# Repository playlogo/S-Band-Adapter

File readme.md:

# S-Band Adapter

*(image might be outdated, check interactive viewer for latest version)*

**Notes:**

- Under 10x10 cm
- Designed to get stacked *on top* of the S-Band module
- Passes ERC & DRC

**Links:**

- [Interactive PCB View (powered by KiCanvas, always up to date)](https://kicanvas.org/?repo=https%3A%2F%2Fgithub.com%2Fplaylogo%2FS-Band-Adapter%2Ftree%2Fmaster%2Fpcb%2FS-Band%2520Adapter)

## Components

**SMD Parts:**

- 2x [`CT3151SP`](https://www.digikey.de/de/products/detail/cal-test-electronics/CT3151SP-2/6005547): Banana plugs for VBat & GND - *[footprint](https://componentsearchengine.com/part-view/CT3151SP-2/Cal%20Test)*
- 1x [`FTSH‑107‑01‑L‑DV‑K‑A`](https://www.digikey.de/de/products/detail/samtec-inc/FTSH-107-01-L-DV-K-A/7443623): ST-Link debug connector, uses UART A from PC104 - *[footprint](https://www.snapeda.com/parts/FTSH-107-01-L-DV-K-A/Samtec%20Inc./view-part/?welcome=home&ref=digikey)*
- 1x [`ERF8-030-05.0-L-DV-TR`](https://www.digikey.de/de/products/detail/samtec-inc/ERF8-030-05-0-L-DV-TR/6613294): Move Backplane connector - *[footprint](https://www.snapeda.com/parts/ERF8-030-05.0-L-DV-TR/Samtec%20Inc./view-part/?ref=digikey)*
- 1x [`Molex 53261–1071 10pin`](https://www.digikey.de/de/products/detail/molex/0532611071/699102): S-Band MCU Debug Connector - Same MCU Debug connector on S-Band module - *[footprint](https://www.snapeda.com/parts/532611071/Molex/view-part/?ref=digikey)*
- S-Band connector:
  - Either set of two proper 52 Pin 2.54 Pitch connectors like [these overpriced ones (ESQ-126-39-G-D)](https://www.digikey.de/de/products/detail/samtec-inc/ESQ-126-39-G-D/3601055)
  - Or just a bunch of female and male 2.54mm Pitch connectors cut and combined to get 4 rows x 26 Pins (female for S-Band board, male for this Adapter) - maybe bad idea, since you then cannot stack more than one board on top of the S-Band module...
- 1x 0805 100nF capacitor
- 1x Würth 430152050826 Tactile Switch

**Cables:**

- Adapter Backplane female to Backplane female: Possibly a [Samtec ERCD with 30pos ? - looks very expensive, who even selected the Backplane connector, maybe they know which cable to use...](https://www.samtec.com/products/ercd#)
- S-Band MCU Debug Connector: [Molex PicoBlade 1.25mm, Female-to-Female, 300.00mm Length, 10 Circuits](https://www.molex.com/en-us/products/part-detail/151341003) - Pin order on one side has to be reversed... See image below, `C` should come out on the 3rd from the bottom and not 3rd from top, can easily be done with a screwdrivers

## Schematic

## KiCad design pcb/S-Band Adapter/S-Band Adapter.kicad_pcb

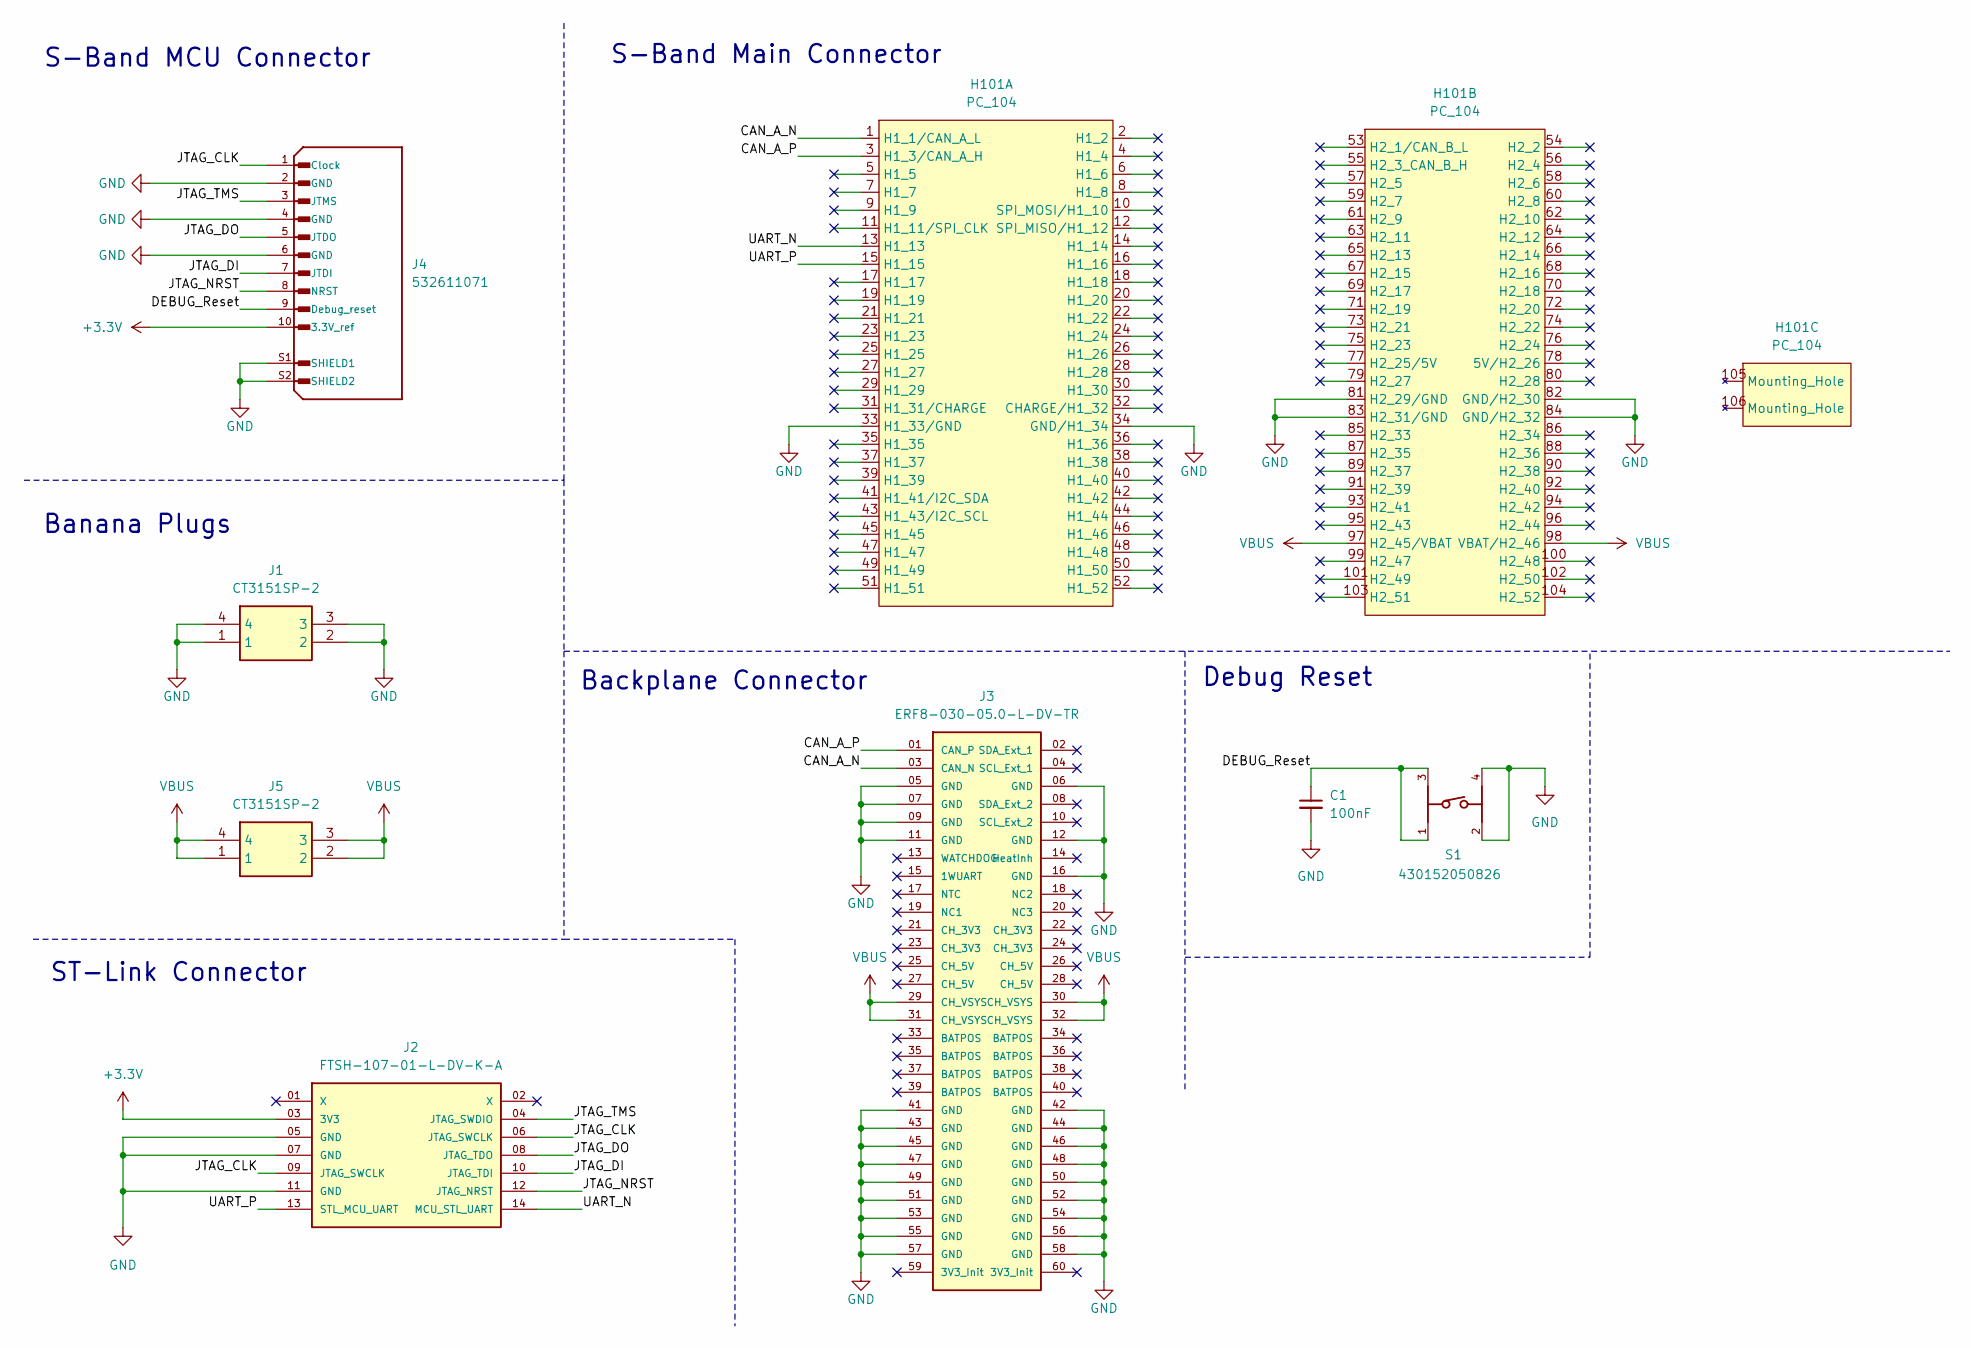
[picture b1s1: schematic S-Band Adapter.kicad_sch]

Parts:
C1: 100nF; C_0805_2012Metric_Pad1.18x1.45mm_HandSolder
H101: PC_104; PartNumber ESQ-126-39-x-D
J1, J5: CT3151SP-2; CT3151SP2; Manufacturer_Part_Number CT3151SP-2; Mouser Part Number 510-CT3151SP-2
J2: FTSH-107-01-L-DV-K-A; SAMTEC_FTSH-107-01-L-DV-K-A; PARTREV H; DigiKey_Part_Number FTSH-107-01-L-DV-K-A-ND
J3: ERF8-030-05.0-L-DV-TR; SAMTEC_ERF8-030-05.0-L-DV-TR; DigiKey_Part_Number SAM13580CT-ND
J4: 532611071; MOLEX_532611071; PARTREV J; DigiKey_Part_Number WM7628CT-ND
S1: 430152050826; DigiKey_Part_Number 732-6993-1-ND

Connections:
+3.3V: J2.03 (3V3), J4.10 (3.3V_ref)
/CAN_A_N: H101.1 (H1_1/CAN_A_L), J3.03 (CAN_N)
/CAN_A_P: H101.3 (H1_3/CAN_A_H), J3.01 (CAN_P)
/DEBUG_Reset: C1.1, J4.9 (Debug_reset), S1.1, S1.3
/JTAG_CLK: J2.06 (JTAG_SWCLK), J2.09 (JTAG_SWCLK), J4.1 (Clock)
/JTAG_DI: J2.10 (JTAG_TDI), J4.7 (JTDI)
/JTAG_DO: J2.08 (JTAG_TDO), J4.5 (JTDO)
/JTAG_NRST: J2.12 (JTAG_NRST), J4.8 (NRST)
/JTAG_TMS: J2.04 (JTAG_SWDIO), J4.3 (JTMS)
/UART_N: H101.13 (H1_13), J2.14 (MCU_STL_UART)
/UART_P: H101.15 (H1_15), J2.13 (STL_MCU_UART)
GND: C1.2, H101.33 (H1_33/GND), H101.34 (GND/H1_34), H101.81 (H2_29/GND), H101.82 (GND/H2_30), H101.83 (H2_31/GND), H101.84 (GND/H2_32), J1.1, J1.2, J1.3, J1.4, J2.05 (GND), J2.07 (GND), J2.11 (GND), J3.05 (GND), J3.06 (GND), J3.07 (GND), J3.09 (GND), J3.11 (GND), J3.12 (GND), J3.16 (GND), J3.41 (GND), J3.42 (GND), J3.43 (GND), J3.44 (GND), J3.45 (GND), J3.46 (GND), J3.47 (GND), J3.48 (GND), J3.49 (GND), J3.50 (GND), J3.51 (GND), J3.52 (GND), J3.53 (GND), J3.54 (GND), J3.55 (GND), J3.56 (GND), J3.57 (GND), J3.58 (GND), J4.2 (GND), J4.4 (GND), J4.6 (GND), J4.S1 (SHIELD1), J4.S2 (SHIELD2), S1.2, S1.4
VBUS: H101.97 (H2_45/VBAT), H101.98 (VBAT/H2_46), J3.29 (CH_VSYS), J3.30 (CH_VSYS), J3.31 (CH_VSYS), J3.32 (CH_VSYS), J5.1, J5.2, J5.3, J5.4

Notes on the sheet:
ST-Link Connector
S-Band MCU Connector
Debug Reset
Banana Plugs
S-Band Main Connector
Backplane Connector

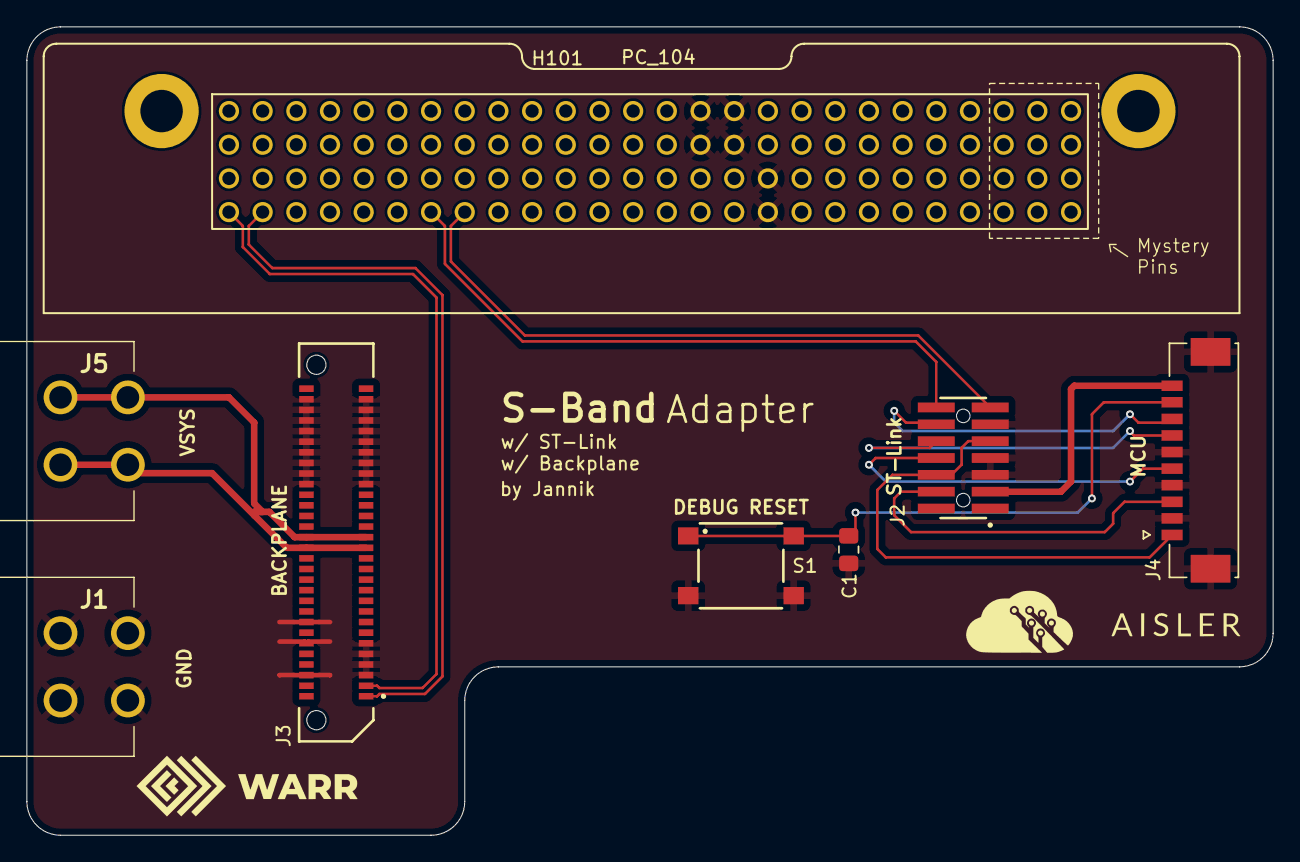
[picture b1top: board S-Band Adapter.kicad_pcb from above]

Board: 2 copper layers, 94.0 x 61.0 mm, 8 parts (0 on the bottom side), 13 nets.

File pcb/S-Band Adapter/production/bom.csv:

Designator,Footprint,Quantity,Value,LCSC Part #
C1,0805,1,100nF,
H101,PC_104,1,PC_104,
"J1, J5",CT3151SP2,2,CT3151SP-2,
J2,SAMTEC_FTSH-107-01-L-DV-K-A,1,FTSH-107-01-L-DV-K-A,
J3,SAMTEC_ERF8-030-05.0-L-DV-TR,1,ERF8-030-05.0-L-DV-TR,
J4,MOLEX_532611071,1,532611071,
S1,430152050826,1,430152050826,

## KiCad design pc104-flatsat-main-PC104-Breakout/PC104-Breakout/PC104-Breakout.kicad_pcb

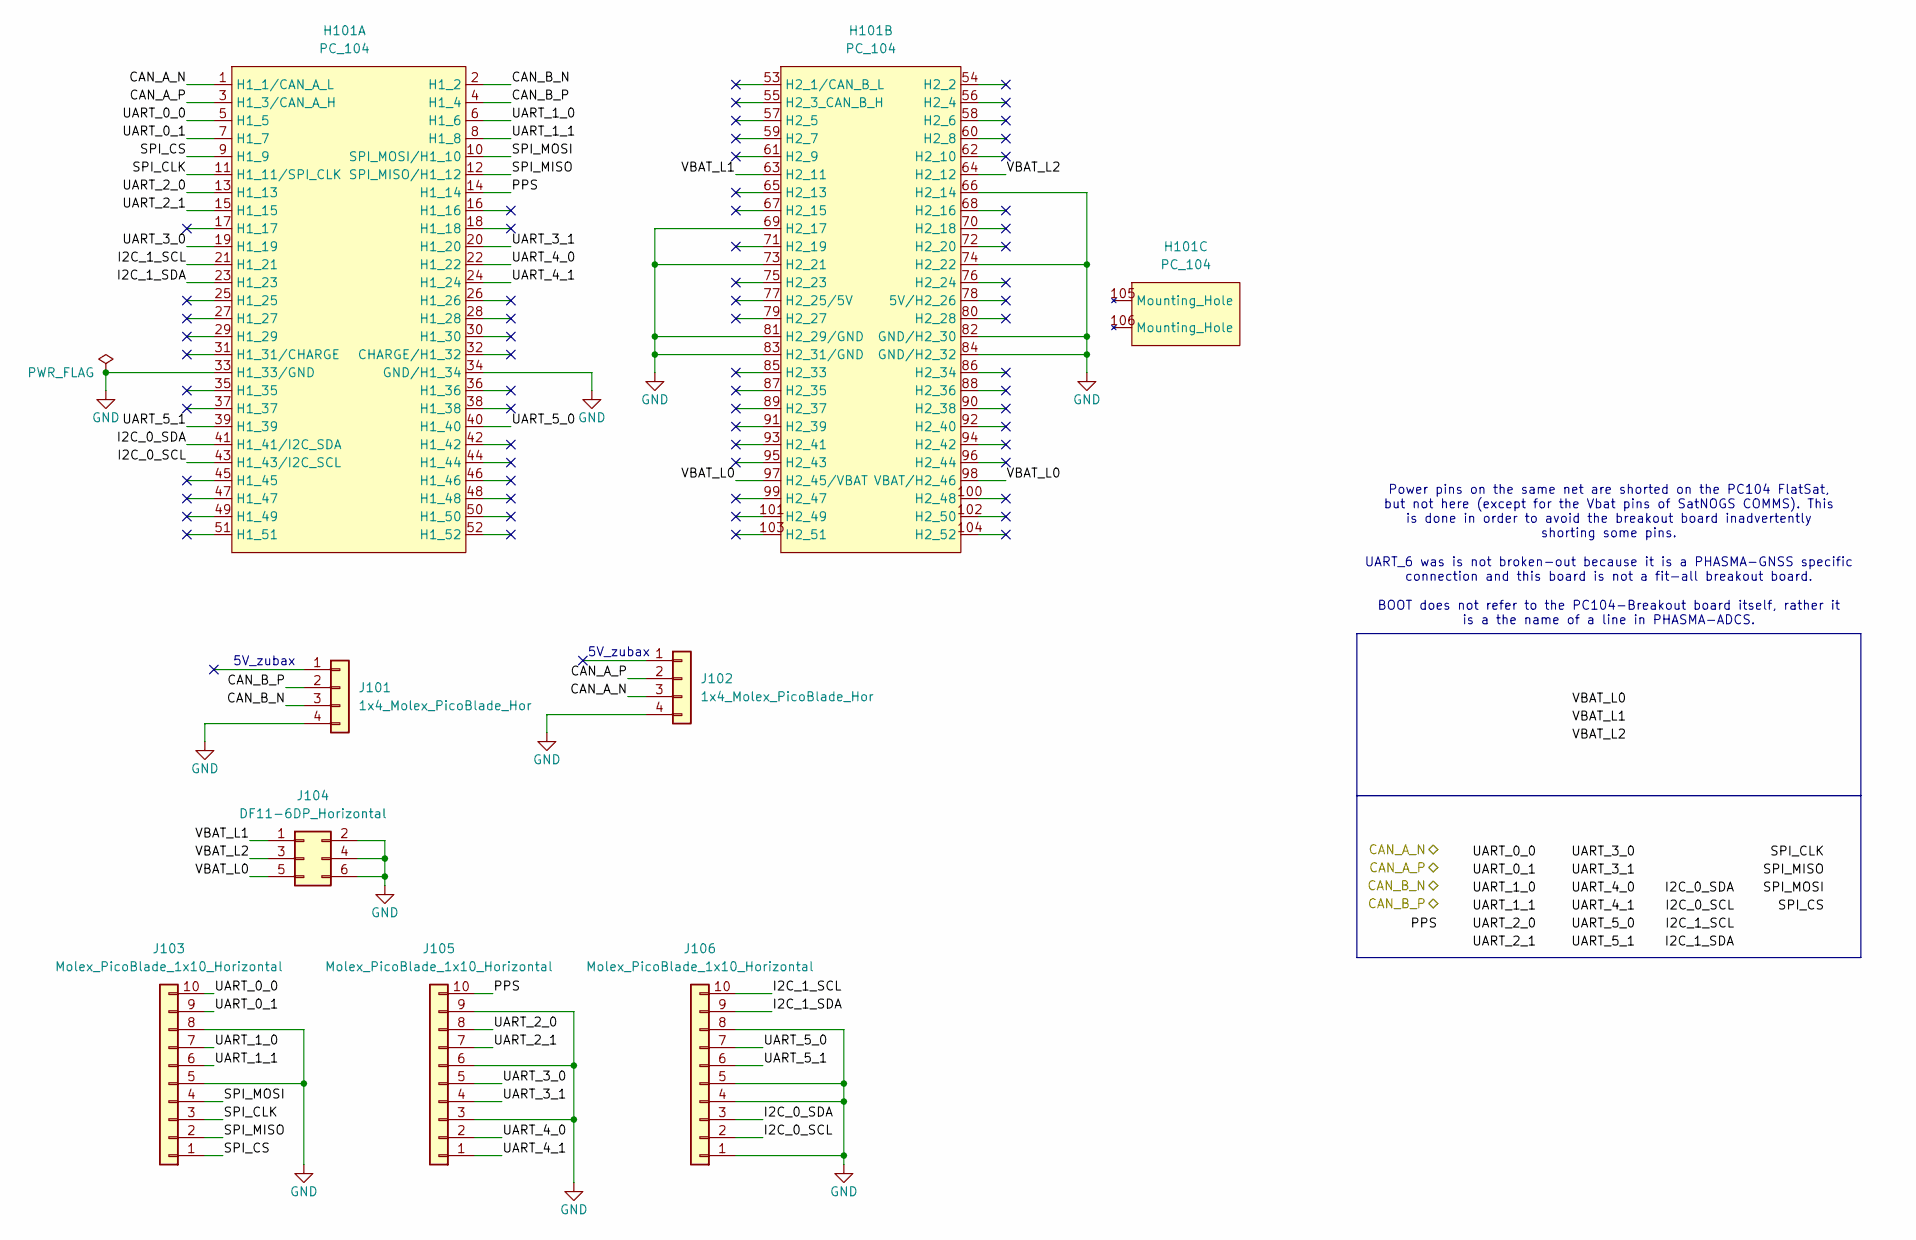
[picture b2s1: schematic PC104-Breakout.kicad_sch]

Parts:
H101: PC_104; PartNumber ESQ-126-39-x-D
J101, J102: 1x4_Molex_PicoBlade_Hor; Molex_PicoBlade_53261-0471_1x04-1MP_P1.25mm_Horizontal; PartNumber 53261-0471
J103, J105, J106: Molex_PicoBlade_1x10_Horizontal; Molex_PicoBlade_53261-1071_1x10-1MP_P1.25mm_Horizontal; PartNumber 53261-1071
J104: DF11-6DP_Horizontal; hrs-df11-6dp-2ds; PartNumber DF11-6DP-2DS(52)

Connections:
/CAN_A_N: H101.1 (H1_1/CAN_A_L), J102.3
/CAN_A_P: H101.3 (H1_3/CAN_A_H), J102.2
/CAN_B_N: H101.2 (H1_2), J101.3
/CAN_B_P: H101.4 (H1_4), J101.2
/I2C_0_SCL: H101.43 (H1_43/I2C_SCL), J106.2
/I2C_0_SDA: H101.41 (H1_41/I2C_SDA), J106.3
/I2C_1_SCL: H101.21 (H1_21), J106.10
/I2C_1_SDA: H101.23 (H1_23), J106.9
/PPS: H101.14 (H1_14), J105.10
/SPI_CLK: H101.11 (H1_11/SPI_CLK), J103.3
/SPI_CS: H101.9 (H1_9), J103.1
/SPI_MISO: H101.12 (SPI_MISO/H1_12), J103.2
/SPI_MOSI: H101.10 (SPI_MOSI/H1_10), J103.4
/UART_0_0: H101.5 (H1_5), J103.10
/UART_0_1: H101.7 (H1_7), J103.9
/UART_1_0: H101.6 (H1_6), J103.7
/UART_1_1: H101.8 (H1_8), J103.6
/UART_2_0: H101.13 (H1_13), J105.8
/UART_2_1: H101.15 (H1_15), J105.7
/UART_3_0: H101.19 (H1_19), J105.5
/UART_3_1: H101.20 (H1_20), J105.4
/UART_4_0: H101.22 (H1_22), J105.2
/UART_4_1: H101.24 (H1_24), J105.1
/UART_5_0: H101.40 (H1_40), J106.7
/UART_5_1: H101.39 (H1_39), J106.6
/VBAT_L0: H101.97 (H2_45/VBAT), H101.98 (VBAT/H2_46), J104.5
/VBAT_L1: H101.63 (H2_11), J104.1
/VBAT_L2: H101.64 (H2_12), J104.3
GND: H101.33 (H1_33/GND), H101.34 (GND/H1_34), H101.66 (H2_14), H101.69 (H2_17), H101.73 (H2_21), H101.74 (H2_22), H101.81 (H2_29/GND), H101.82 (GND/H2_30), H101.83 (H2_31/GND), H101.84 (GND/H2_32), J101.4, J102.4, J103.5, J103.8, J104.2, J104.4, J104.6, J105.3, J105.6, J105.9, J106.1, J106.4, J106.5, J106.8

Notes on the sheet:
5V_zubax
Power pins on the same net are shorted on the PC104 FlatSat, but not here (except for the Vbat pins of SatNOGS COMMS). This is done in order to avoid the breakout board inadvertently shorting some pins. UART_6 was is not broken-out because it is a PHASMA-GNSS specific connection and this board is n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

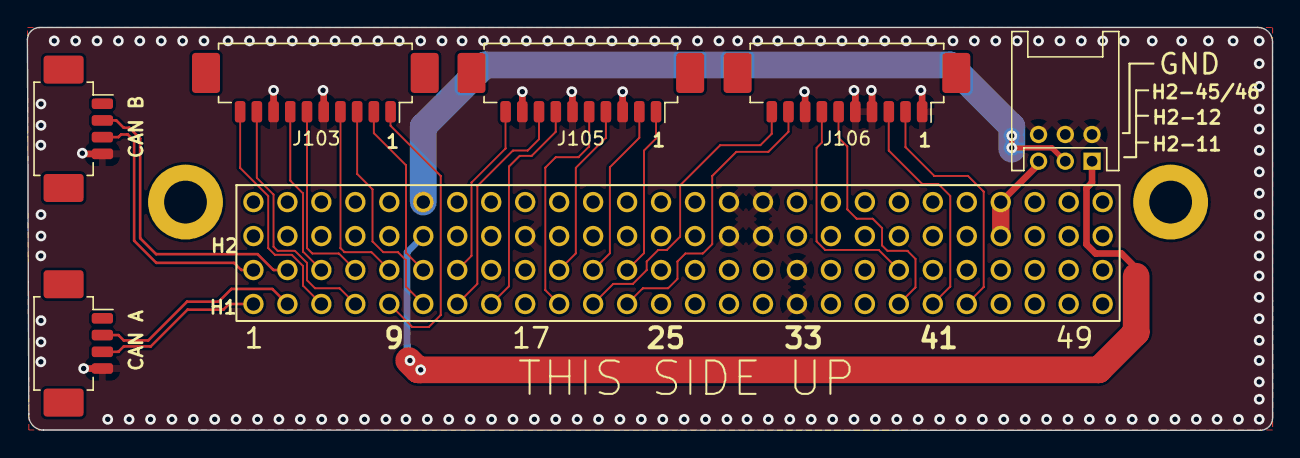
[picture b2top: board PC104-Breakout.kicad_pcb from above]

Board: 2 copper layers, 93.1 x 30.1 mm, 7 parts (0 on the bottom side), 29 nets.

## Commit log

2026-02-22 push
2026-02-22 Finished PCB
2026-02-22 Improved docs
2026-02-22 Docs..
2026-02-22 Fixed Pulling VSYS from BATPOS
2026-02-22 Improved 3.3V net track width
2026-02-22 Added Debug_Reset button & fixed VBAT label
2026-02-22 Updated pcb image
2026-02-22 Added aisler logo
2026-02-23 Added components section to docs
